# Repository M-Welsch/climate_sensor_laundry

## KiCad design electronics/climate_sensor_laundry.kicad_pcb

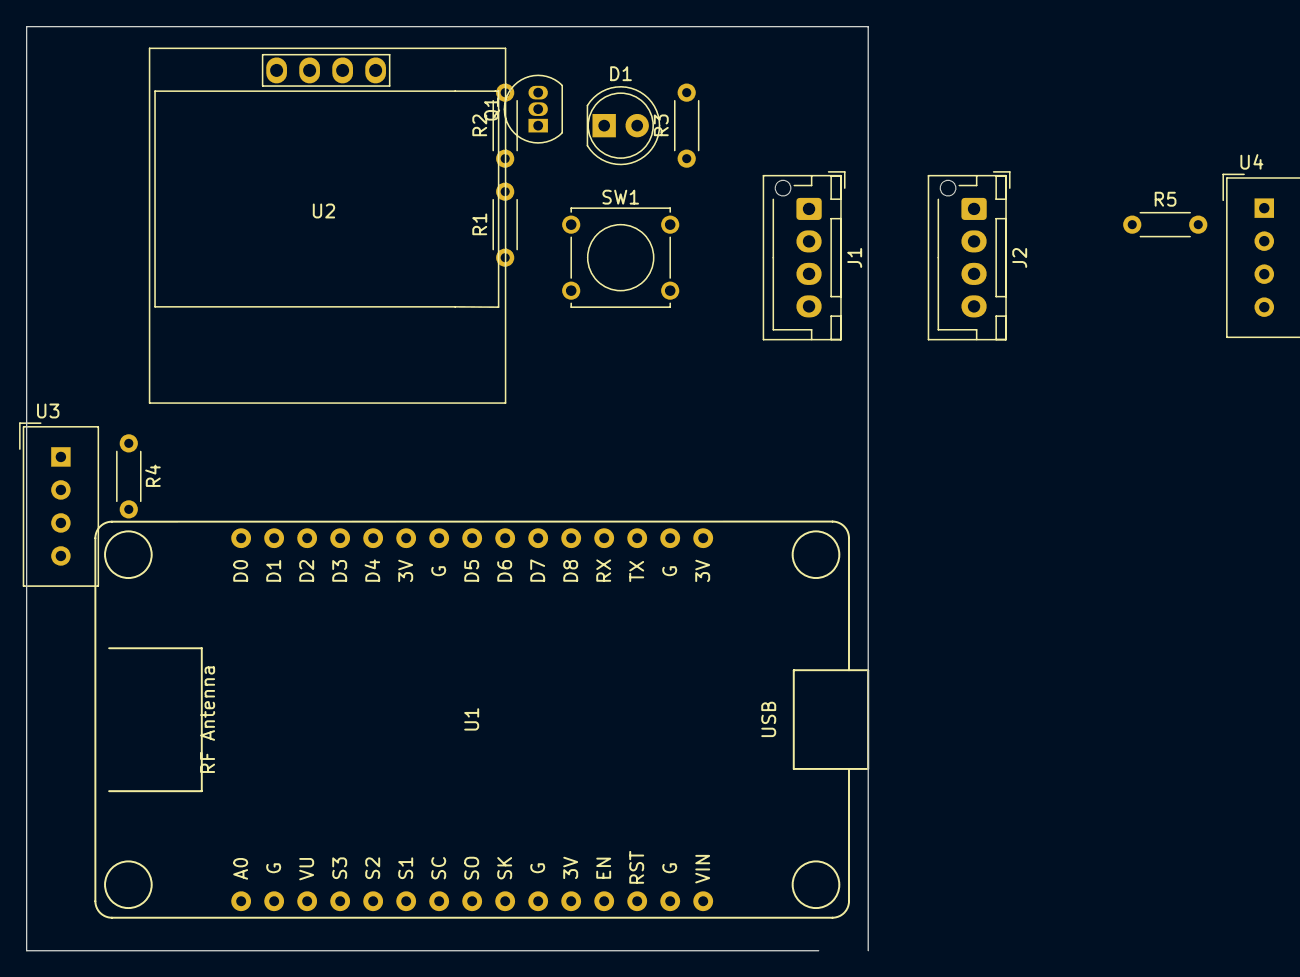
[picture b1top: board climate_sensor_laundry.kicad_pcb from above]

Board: 2 copper layers, 64.8 x 71.1 mm, 14 parts (0 on the bottom side), 12 nets, no tracks yet.

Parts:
D1: green; LED_D5.0mm
J1, J2: Conn_01x04; JST_XH_B4B-XH-AM_1x04_P2.50mm_Vertical
Q1: BS170; TO-92_Inline
R1, R4, R5: 1k; R_Axial_DIN0204_L3.6mm_D1.6mm_P5.08mm_Horizontal
R2: 47k; R_Axial_DIN0204_L3.6mm_D1.6mm_P5.08mm_Horizontal
R3: 100; R_Axial_DIN0204_L3.6mm_D1.6mm_P5.08mm_Horizontal
SW1: SW_Push; SW_Tactile_Straight_KSA0Axx1LFTR
U1: NodeMCU1.0(ESP-12E); NodeMCU1.0(12-E)
U2: display_i2c_1inch3
U3, U4: DHT22; Aosong_DHT11_5.5x12.0_P2.54mm

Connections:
+3V3: J1.1, J2.1, R3.1, R4.1, R5.1, U1.11 (3.3V), U1.16 (3.3V), U1.25 (3.3V), U2.1 (VDD), U3.1 (VCC), U4.1 (VCC)
/button: SW1.1, SW1.2, U1.21 (D7(GPIO13))
/dht_inside: R4.2, U1.23 (D5(GPIO14)), U3.2 (IO)
/dht_outside: J1.2, J2.2, R5.2, U1.22 (D6(GPIO12)), U4.2 (IO)
/led_green: R1.1, U1.20 (D8(GPIO15))
/scl: U1.29 (D1(GPIO5)), U2.3 (SCL)
/sda: U1.28 (D2(GPIO4)), U2.4 (SDA)
/spare_pin: J1.3, U1.27 (D3(GPIO0))
GND: J1.4, J2.4, Q1.3 (S), R2.2, U1.10 (GND), U1.14 (GND), U1.17 (GND), U1.24 (GND), U2.2 (VSS), U3.4 (GND), U4.4 (GND)
unnamed: D1.1 (K), Q1.1 (D)
unnamed: D1.2 (A), R3.2
unnamed: Q1.2 (G), R1.2, R2.1

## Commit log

2022-03-14 display works
2022-03-15 correct display of degree sign character works
2022-03-15 write class for display
2022-03-15 refactor display class
2022-03-22 add temperature sensor
2022-03-22 refactor temperature_sensor
2022-03-22 add battery monitoring (adc readout, no real monitoring yet)
2022-03-23 move display to lib
2022-03-23 implement adc digit to voltage calculation
2022-03-23 implement skeleton for web_server. it already connects to wifi
2022-03-23 implement webserver that sends basic response
2022-03-23 implement send data over air
2022-03-24 add logging, beautify html output
2022-05-14 add rest api for temperature and battery values
2022-05-14 refactor json builtup
2022-05-15 implement undervoltage lockout
2022-08-15 minimal working mqtt sender
2022-08-15 slightly more clean mqtt approach
2022-08-15 first sketch, not working properly
2022-08-17 minimally working
2022-08-17 dht in its own file
2022-08-17 add led and button
2022-08-17 get rid of useless printout
2022-08-18 mqtt publishing works
2022-08-20 update labels
2022-08-22 implement dewpoint calculation
2022-08-22 add dewpoint calculation
2022-08-23 implement dewpoint logic, wifi mananger
2022-09-26 refactor dht into class
2022-09-26 display statemachine
2022-11-08 restructure
2022-12-27 works with external sensor over network
2022-12-27 code cleanup
